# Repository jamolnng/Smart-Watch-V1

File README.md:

# Smart Watch

An open source smart watch based on a PIC32 microcontroller. The original idea came from http://jared.geek.nz/2014/jul/oshw-oled-watch and many of the design ideas came from here

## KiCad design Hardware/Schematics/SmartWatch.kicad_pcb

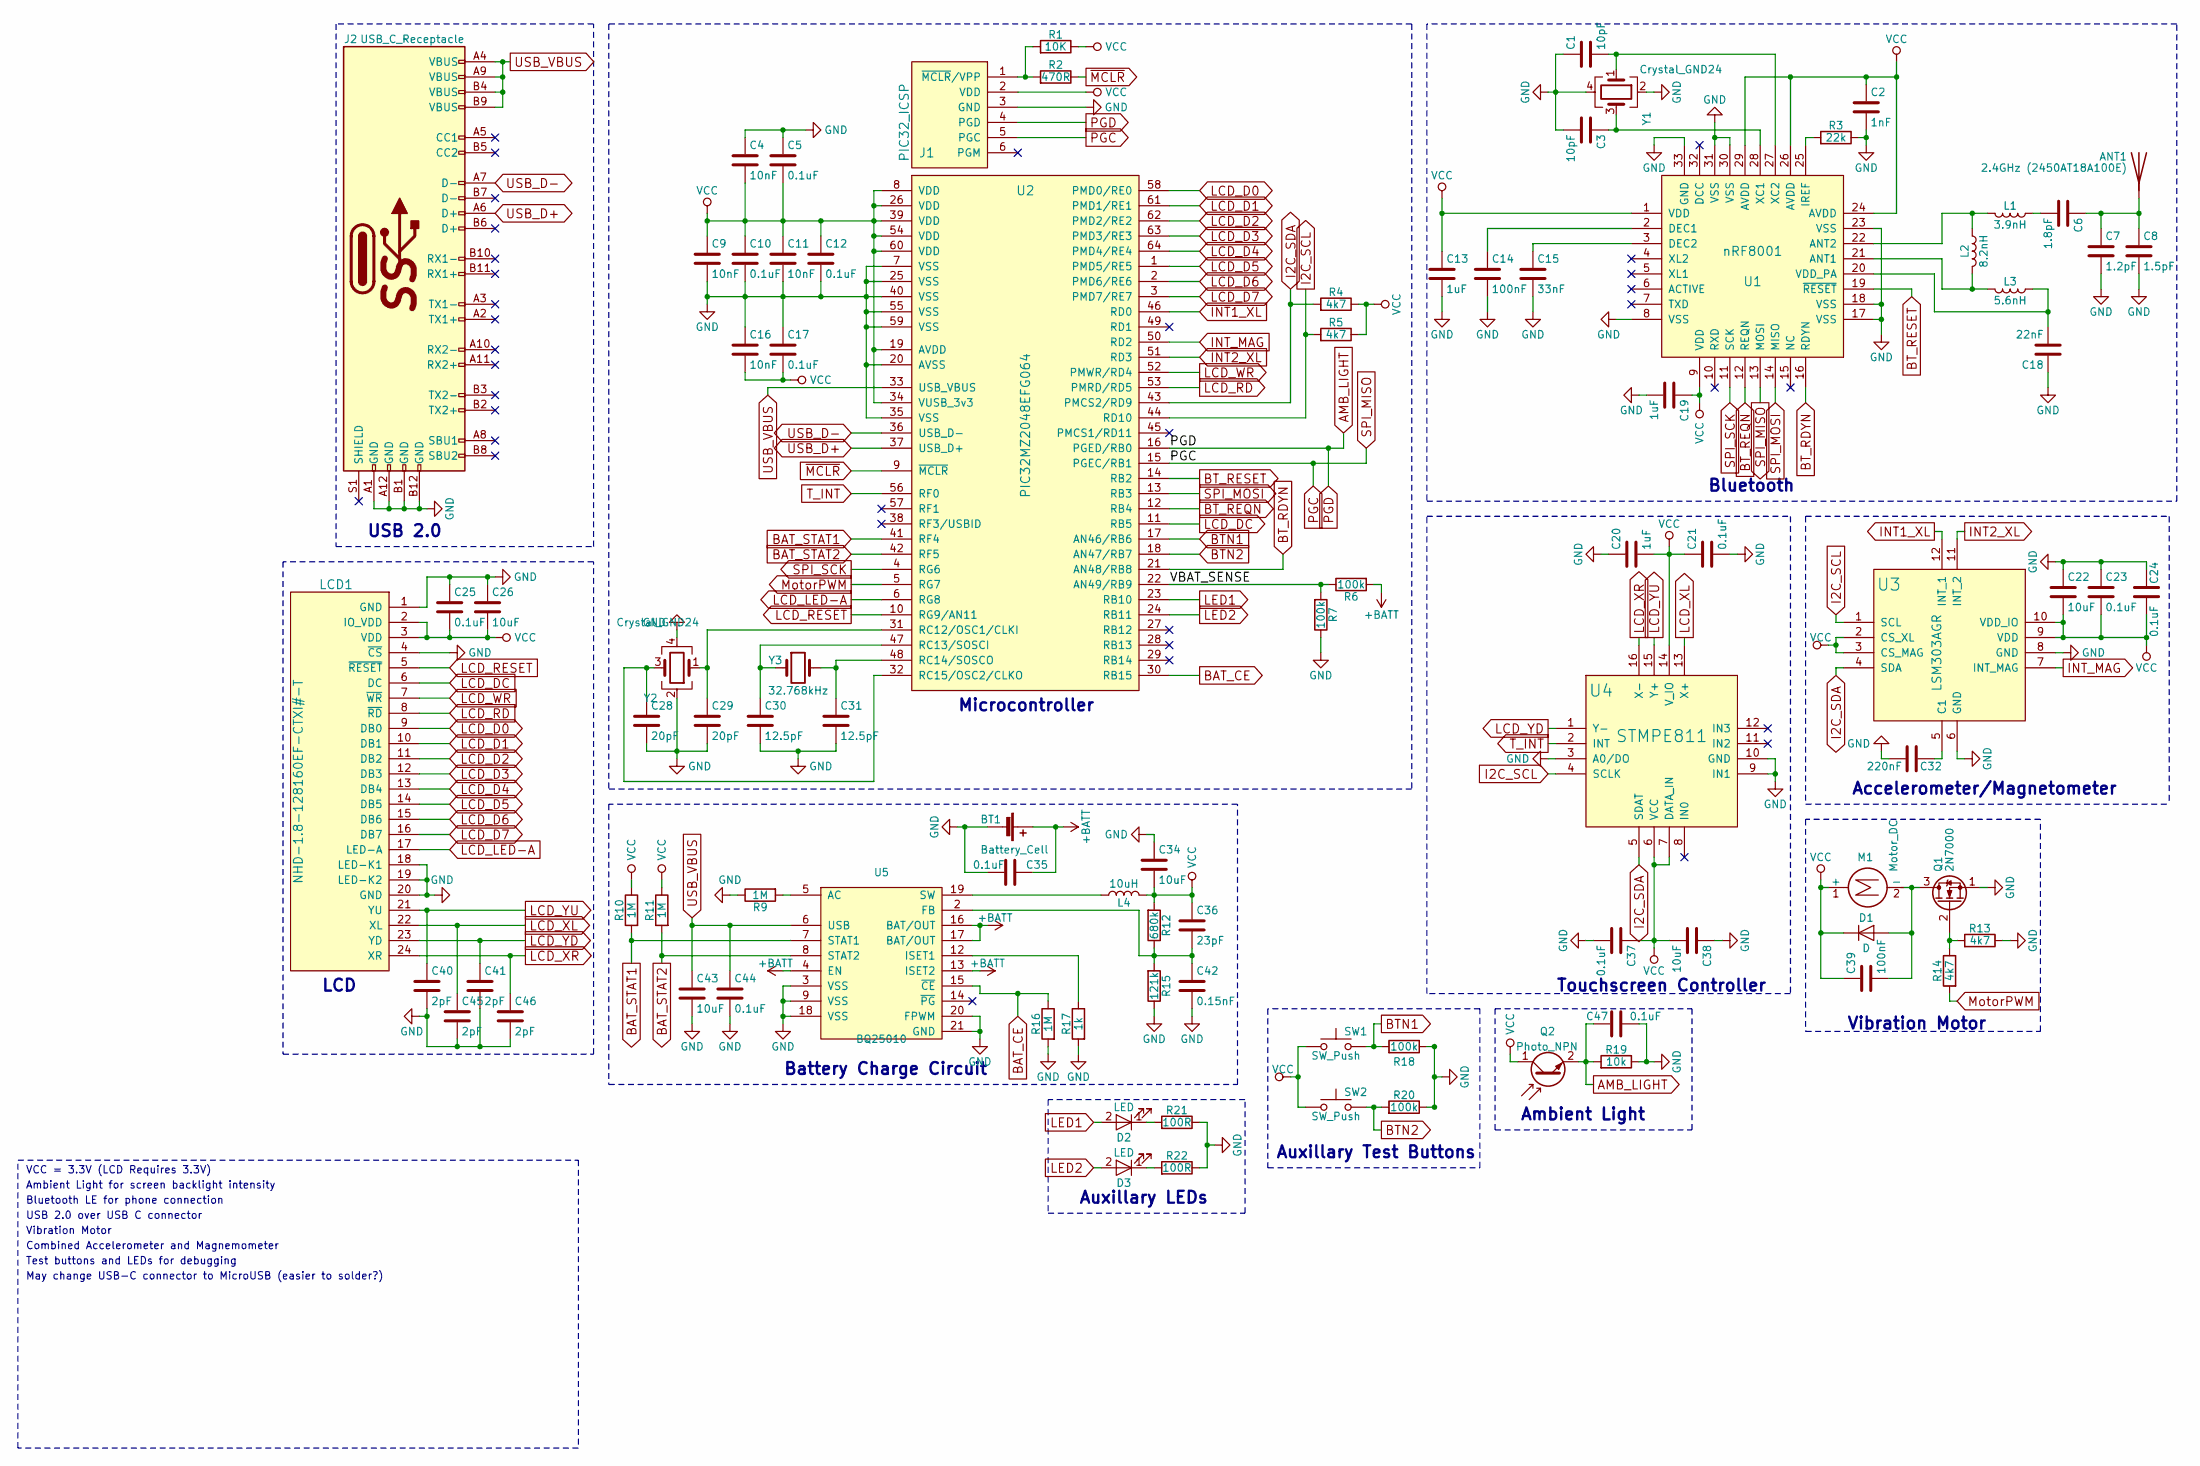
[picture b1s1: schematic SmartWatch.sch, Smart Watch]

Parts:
ANT1: 2.4GHz (2450AT18A100E); 2450AT18A100E
BT1: Battery_Cell; Pin_Header_Straight_2x01_Pitch2.54mm_SMD
C1, C3: 10pF; C_0603
C2: 1nF; C_0603
C4, C9, C11, C16: 10nF; C_0603
C5, C10, C12, C17, C21, C23, C24, C25, C35, C37, C44, C47: 0.1uF; C_0603
C6: 1.8pF; C_0603
C7: 1.2pF; C_0603
C8: 1.5pF; C_0603
C13, C19, C20: 1uF; C_0603
C14, C39: 100nF; C_0603
C15: 33nF; C_0603
C18: 22nF; C_0603
C22, C26, C34, C38, C43: 10uF; C_0603
C28, C29: 20pF; C_0603
C30, C31: 12.5pF; C_0603
C32: 220nF; C_0603
C36: 23pF; C_0603
C40, C41, C45, C46: 2pF; C_0603
C42: 0.15nF; C_0603
D1: D; D_0603
D2, D3: LED; LED_0603
J1: PIC32_ICSP; Pin_Header_Straight_2x03_Pitch1.00mm_SMD
J2: USB_C_Receptacle; USB_C_Receptacle_Amphenol_12401548E4-2A_CircularHoles
L1: 3.9nH; L_0603
L2: 8.2nH; L_0603
L3: 5.6nH; L_0603
L4: 10uH; L_0603
LCD1: NHD-1.8-128160EF-CTXI#-T
M1: Motor_DC; Pin_Header_Straight_2x01_Pitch2.54mm_SMD
Q1: 2N7000; TO-92_Molded_Narrow
Q2: Photo_NPN; D_3220
R1: 10K; R_0603
R2: 470R; R_0603
R3: 22k; R_0603
R4, R5, R13, R14: 4k7; R_0603
R6, R7, R18, R20: 100k; R_0603
R9, R10, R11, R16: 1M; R_0603
R12: 680k; R_0603
R15: 121k; R_0603
R17: 1k; R_0603
R19: 10k; R_0603
R21, R22: 100R; R_0603
SW1, SW2: SW_Push; SW_SPST_FSMSM
U1: nRF8001; QFN-32-1EP_5x5mm_Pitch0.5mm
U2: PIC32MZ2048EFG064; TQFP-64_10x10mm_Pitch0.5mm
U3: LSM303AGR; LGA-12_2x2mm_Pitch0.5mm
U4: STMPE811; QFN-20-1EP_4x4mm_Pitch0.5mm
U5: BQ25010; pvqfn-n20
Y1, Y2: Crystal_GND24; CX2520DB16000F0FDFC1
Y3: 32.768kHz; TFA322PG327KR

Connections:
+BATT: BT1.1 (+), C35.1, R6.2, U5.4 (EN), U5.13 (ISET2), U5.16 (BAT/OUT), U5.17 (BAT/OUT)
/VBAT_SENSE: R6.1, R7.2, U2.22 (AN49/RB9)
AMB_LIGHT: C47.1, J1.4 (PGD), Q2.2 (E), R19.2, U2.16 (PGED/RB0)
BAT_CE: R16.1, U2.30 (RB15), U5.15 (~CE)
BAT_STAT1: R10.2, U2.41 (RF4), U5.7 (STAT1)
BAT_STAT2: R11.2, U2.42 (RF5), U5.8 (STAT2)
BTN1: R18.2, SW1.2, U2.17 (AN46/RB6)
BTN2: R20.2, SW2.2, U2.18 (AN47/RB7)
BT_RDYN: U1.16 (RDYN), U2.21 (AN48/RB8)
BT_REQN: U1.12 (REQN), U2.12 (RB4)
BT_RESET: U1.19 (~RESET), U2.14 (RB2)
GND: BT1.2 (-), C1.1, C2.2, C3.2, C4.1, C5.1, C7.2, C8.2, C9.2, C10.2, C11.2, C12.2, C13.2, C14.2, C15.2, C16.1, C17.1, C18.1, C19.2, C20.1, C21.2, C22.1, C23.1, C24.1, C25.1, C26.1, C28.2, C29.2, C30.2, C31.2, C32.2, C34.1, C35.2, C37.2, C38.1, C40.2, C41.2, C42.2, C43.2, C44.2, C45.2, C46.2, C47.2, J1.3 (GND), J2.A1 (GND), J2.A12 (GND), J2.B1 (GND), J2.B12 (GND), LCD1.1 (GND), LCD1.4 (~CS), LCD1.18 (LED-K1), LCD1.19 (LED-K2), LCD1.20 (GND), Q1.1 (S), R3.1, R7.1, R9.1, R13.1, R15.1, R16.2, R17.2, R18.1, R19.1, R20.1, R21.1, R22.1, U1.8 (VSS), U1.17 (VSS), U1.18 (VSS), U1.23 (VSS), U1.30 (VSS), U1.31 (VSS), U1.33 (GND), U2.7 (VSS), U2.20 (AVSS), U2.25 (VSS), U2.35 (VSS), U2.40 (VSS), U2.55 (VSS), U2.59 (VSS), U3.6 (GND), U3.8 (GND), U4.3 (A0/DO), U4.9 (IN1), U4.10 (GND), U5.3 (VSS), U5.9 (VSS), U5.18 (VSS), U5.20 (FPWM), U5.21 (GND), Y1.2, Y1.4, Y2.2, Y2.4; also elsewhere on the board
I2C_SCL: R5.2, U2.44 (RD10), U3.1 (SCL), U4.4 (SCLK)
I2C_SDA: R4.2, U2.43 (PMCS2/RD9), U3.4 (SDA), U4.5 (SDAT)
INT1_XL: U2.46 (RD0), U3.12 (INT_1)
INT2_XL: U2.51 (RD3), U3.11 (INT_2)
INT_MAG: U2.50 (RD2), U3.7 (INT_MAG)
LCD_D0: LCD1.9 (DB0), U2.58 (PMD0/RE0)
LCD_D1: LCD1.10 (DB1), U2.61 (PMD1/RE1)
LCD_D2: LCD1.11 (DB2), U2.62 (PMD2/RE2)
LCD_D3: LCD1.12 (DB3), U2.63 (PMD3/RE3)
LCD_D4: LCD1.13 (DB4), U2.64 (PMD4/RE4)
LCD_D5: LCD1.14 (DB5), U2.1 (PMD5/RE5)
LCD_D6: LCD1.15 (DB6), U2.2 (PMD6/RE6)
LCD_D7: LCD1.16 (DB7), U2.3 (PMD7/RE7)
LCD_DC: LCD1.6 (DC), U2.11 (RB5)
LCD_LED-A: LCD1.17 (LED-A), U2.6 (RG8)
LCD_RD: LCD1.8 (~RD), U2.53 (PMRD/RD5)
LCD_RESET: LCD1.5 (~RESET), U2.10 (RG9/AN11)
LCD_WR: LCD1.7 (~WR), U2.52 (PMWR/RD4)
LCD_XL: C45.1, LCD1.22 (XL), U4.13 (X+)
LCD_XR: C46.1, LCD1.24 (XR), U4.16 (X-)
LCD_YD: C41.1, LCD1.23 (YD), U4.1 (Y-)
LCD_YU: C40.1, LCD1.21 (YU), U4.15 (Y+)
LED1: D2.2 (A), U2.23 (RB10)
LED2: D3.2 (A), U2.24 (RB11)
MotorPWM: R14.2, U2.5 (RG7)
unnamed: ANT1.1, C6.1, C7.1, C8.1
unnamed: C1.2, U1.27 (XC2), Y1.1
unnamed: C3.1, U1.28 (XC1), Y1.3
unnamed: C6.2, L1.1
unnamed: C14.1, U1.2 (DEC1)
unnamed: C15.1, U1.3 (DEC2)
unnamed: C18.2, L3.1, U1.20 (VDD_PA)
unnamed: C28.1, U2.32 (RC15/OSC2/CLKO), Y2.3
unnamed: C29.1, U2.31 (RC12/OSC1/CLKI), Y2.1
unnamed: C30.1, U2.47 (RC13/SOSCI), Y3.1
unnamed: C31.1, U2.48 (RC14/SOSCO), Y3.2
unnamed: C32.1, U3.5 (C1)
unnamed: C36.2, C42.1, R12.1, R15.2, U5.2 (FB)
unnamed: C39.2, D1.2 (A), M1.2 (-), Q1.3 (D)
unnamed: D2.1 (K), R21.2
unnamed: D3.1 (K), R22.2
unnamed: J1.1 (~MCLR~/VPP), R1.2, R2.2
unnamed: L1.2, L2.1, U1.22 (ANT2)
unnamed: L2.2, L3.2, U1.21 (ANT1)
unnamed: L4.1, U5.19 (SW)
unnamed: Q1.2 (G), R13.2, R14.1
unnamed: R3.2, U1.25 (IREF)
unnamed: R9.2, U5.5 (AC)
unnamed: R17.1, U5.12 (ISET1)
PGC: J1.5 (PGC), U1.13 (MOSI), U2.15 (PGEC/RB1)
SPI_MOSI: U1.14 (MISO), U2.13 (RB3)
SPI_SCK: U1.11 (SCK), U2.4 (RG6)
T_INT: U2.56 (RF0), U4.2 (INT)
USB_D+: J2.A6 (D+), U2.37 (USB_D+)
USB_D-: J2.A7 (D-), U2.36 (USB_D-)
USB_VBUS: C43.1, C44.1, J2.A4 (VBUS), J2.A9 (VBUS), J2.B4 (VBUS), J2.B9 (VBUS), U2.33 (USB_VBUS), U5.6 (USB)
VCC: C2.1, C4.2, C5.2, C9.1, C10.1, C11.1, C12.1, C13.1, C16.2, C17.2, C19.1, C20.2, C21.1, C22.2, C23.2, C24.2, C25.2, C26.2, C34.2, C36.1, C37.1, C38.2, C39.1, D1.1 (K), J1.2 (VDD), L4.2, LCD1.2 (IO_VDD), LCD1.3 (VDD), M1.1 (+), Q2.1 (C), R1.1, R4.1, R5.1, R10.1, R11.1, R12.2, SW1.1, SW2.1, U1.1 (VDD), U1.9 (VDD), U1.24 (AVDD), U1.26 (AVDD), U1.29 (AVDD), U2.8 (VDD), U2.19 (AVDD), U2.26 (VDD), U2.34 (VUSB_3v3), U2.39 (VDD), U2.54 (VDD), U2.60 (VDD), U3.2 (CS_XL), U3.3 (CS_MAG), U3.9 (VDD), U3.10 (VDD_IO), U4.6 (VCC), U4.7 (DATA_IN), U4.14 (V_IO); also elsewhere on the board
~MCLR: R2.1, U2.9 (~MCLR)

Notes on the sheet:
Microcontroller
Bluetooth
USB 2.0
Vibration Motor
LCD
Ambient Light
Touchscreen Controller
Accelerometer/Magnetometer
Auxillary Test Buttons
Auxillary LEDs
VCC = 3.3V (LCD Requires 3.3V)
Battery Charge Circuit
Ambient Light for screen backlight intensity
Bluetooth LE for phone connection
USB 2.0 over USB C connector
Combined Accelerometer and Magnemometer
Test buttons and LEDs for debugging
May change USB-C connector to MicroUSB (easier to solder?)

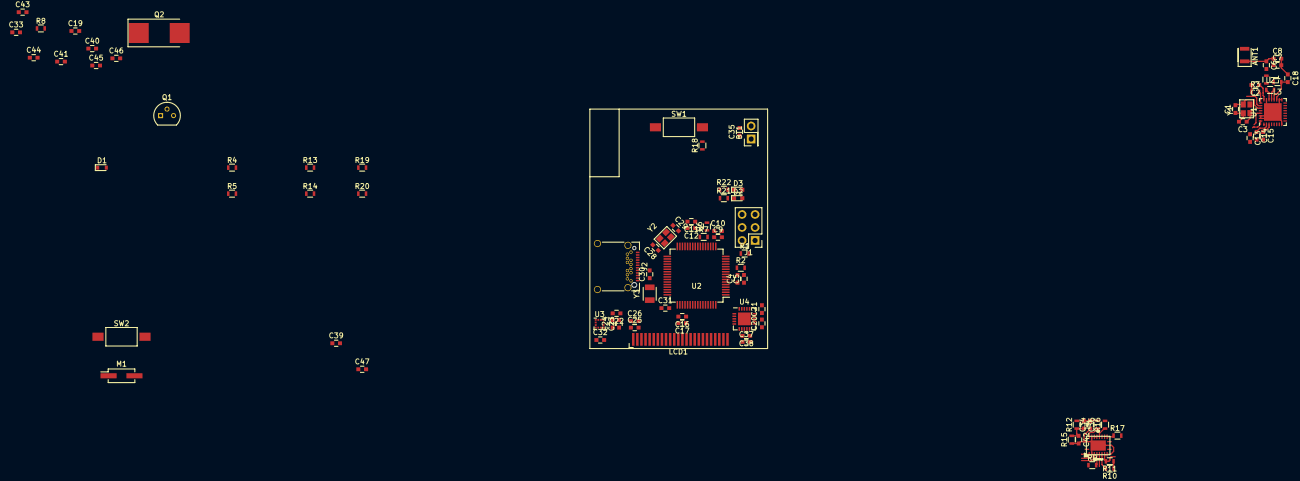
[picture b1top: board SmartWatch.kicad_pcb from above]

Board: 2 copper layers, 93 parts (0 on the bottom side), 70 nets.

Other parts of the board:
C33: 0.1uF; C_0603
R8: 10k; R_0603

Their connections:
GND: C33.2; also elsewhere on the board
VCC: C33.1, R8.1; also elsewhere on the board

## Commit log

2017-12-09 initial commit
    initial commit
2017-12-09 schematic drawing
2017-12-09 schematic image in readme
2017-12-09 change schematic image file type
2017-12-09 datasheets
2017-12-10 gitnore
2017-12-10 pin mapping
    laying out pin mapping in a excel sheet to make it easier to implement
2017-12-10 pin changes
2017-12-10 pin map csv
    csv for easier viewing
2017-12-10 pin mapping
2017-12-14 pin mapping
    removed empty columns
2018-01-15 Update schematic
2018-01-15 Update pin mapping
    All pins have been mapped. Subject to change
2018-01-15 Update Schematic
    Updated schematic to match pin mapping
2018-01-15 Can't append a commit? Lame
2018-01-15 fixed file organization
2018-01-15 finish footprint selecting and started pcb
2018-01-15 Working on schematic
2018-05-27 cant remember
